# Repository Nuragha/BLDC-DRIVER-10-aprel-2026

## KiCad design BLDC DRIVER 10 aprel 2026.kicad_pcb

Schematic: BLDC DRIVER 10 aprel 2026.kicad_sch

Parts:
C1: 4.7uF 35V; C_1206_3216Metric_Pad1.33x1.80mm_HandSolder
C2, C3, C8, C9, C13, C14: 4.7nF 50V; C_1206_3216Metric_Pad1.33x1.80mm_HandSolder
C4, C6, C11: 22pF; C_0805_2012Metric
C5, C10, C15: 470uF/50V; CP_Elec_10x10.5
C7, C12: 4.7uF 24V; C_1206_3216Metric_Pad1.33x1.80mm_HandSolder
C16, C17, C18: 10nF; C_0805_2012Metric
C19, C28, C29: 100nF/35V; C_1206_3216Metric_Pad1.33x1.80mm_HandSolder
C20, C33: 10nF; C_0603_1608Metric_Pad1.08x0.95mm_HandSolder
C23: 22uF/35V; C_1206_3216Metric_Pad1.33x1.80mm_HandSolder
C24, C26, C32, C37: 100nF; C_1206_3216Metric_Pad1.33x1.80mm_HandSolder
C25, C31: 10uF/35V; C_1206_3216Metric_Pad1.33x1.80mm_HandSolder
C27, C34: 100nF; C_0603_1608Metric_Pad1.08x0.95mm_HandSolder
C36: 22uF/10V; C_1206_3216Metric_Pad1.33x1.80mm_HandSolder
C38, C39: 12pF; C_0805_2012Metric
C40, C41: 100nF; C_0805_2012Metric
D2: MM3Z12; D_SOD-323F
D3, D4, D5: UF4007; D_1206_3216Metric_Pad1.42x1.75mm_HandSolder
D6, D9, D11, D12, D16, D17, D21, D25, D26: Green; LED_0805_2012Metric
D7, D8, D13, D14, D18, D19: SR5100; D_0805_2012Metric_Pad1.15x1.40mm_HandSolder
D22, D23, D24: Red; LED_0805_2012Metric
F1: Fuse_Small; Fuse_1206_3216Metric
HQA1: BSC028N06LS3; TDSON-8-1
HQB1: BSC028N06LS3; TDSON-8-1
HQC1: BSC028N06LS3; TDSON-8-1
J1: Conn_01x02_Socket; TerminalBlock_Phoenix_MKDS-1,5-2-5.08_1x02_P5.08mm_Horizont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
J2: Conn_01x03_Socket; TerminalBlock_Phoenix_MKDS-1,5-3_1x03_P5.00mm_Horizontal
J3: Programing Inputs; PinSocket_1x06_P2.54mm_Vertical_SMD_Pin1Left
L1, L2: 6.8uH/4A; L_6.3x6.3_H3
LQA1: BSC028N06LS3; TDSON-8-1
LQB1: BSC028N06LS3; TDSON-8-1
LQC1: BSC028N06LS3; TDSON-8-1
Q7: IRF4905; TO-220-3_Vertical
Q8, Q9, Q10: BCV29; SOT-89-3
R1, R4, R21, R22, R34, R35, R43: 100k; R_0805_2012Metric_Pad1.20x1.40mm_HandSolder
R2, R3, R19, R20, R32, R33: 10R; R_0805_2012Metric_Pad1.20x1.40mm_HandSolder
R5, R6, R24, R25, R37, R38: R10W1; R_1206_3216Metric_Pad1.30x1.75mm_HandSolder
R7, R17, R30: 1k 0.25W; R_0805_2012Metric_Pad1.20x1.40mm_HandSolder
R8, R62: 330R 0.25W; R_0603_1608Metric_Pad0.98x0.95mm_HandSolder
R10, R29: 330R 0.25W; R_0805_2012Metric_Pad1.20x1.40mm_HandSolder
R11: 140k/1%; R_0603_1608Metric_Pad0.98x0.95mm_HandSolder
R12, R16, R18, R26, R28, R48, R51: 10k; R_0805_2012Metric_Pad1.20x1.40mm_HandSolder
R13, R15, R27, R31, R46, R49: 1k; R_0805_2012Metric_Pad1.20x1.40mm_HandSolder
R14, R23, R36: 10mR; R_Shunt_Vishay_WSKW0612
R40, R41, R42: 10; R_0805_2012Metric_Pad1.20x1.40mm_HandSolder
R44: 2.2k; R_0603_1608Metric_Pad0.98x0.95mm_HandSolder
R45, R47, R50: 220; R_0805_2012Metric_Pad1.20x1.40mm_HandSolder
R52: 10k/1%; R_0603_1608Metric_Pad0.98x0.95mm_HandSolder
R53, R57: 470k/1%; R_0603_1608Metric_Pad0.98x0.95mm_HandSolder
R54, R58: 75k/1%; R_0603_1608Metric_Pad0.98x0.95mm_HandSolder
R55, R59: 0R; R_0603_1608Metric_Pad0.98x0.95mm_HandSolder
R56: 1k; R_0603_1608Metric_Pad0.98x0.95mm_HandSolder
R60: 20k/1%; R_0603_1608Metric_Pad0.98x0.95mm_HandSolder
R61: 62k/1%; R_0603_1608Metric_Pad0.98x0.95mm_HandSolder
R63: 100; R_0805_2012Metric_Pad1.20x1.40mm_HandSolder
R64, R65, R66, R67: 22; R_0805_2012Metric_Pad1.20x1.40mm_HandSolder
SW1: Reset Button; SW_SPST_EVQP2_MiddlePushTravel_H2.5mm
U1, U2, U3: IR2110S; SOIC-16W_7.5x10.3mm_P1.27mm
U5: STM32G431CBTx; LQFP-48_7x7mm_P0.5mm
U6, U7: TPS62933F; SOT-583-8
Y1: 48MHz; Crystal_SMD_0603-2Pin_6.0x3.5mm_HandSoldering

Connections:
+3.3V: C36.1, C37.1, C41.1, D9.2 (A), D11.2 (A), D16.2 (A), D26.2 (A), J2.1, L2.2, Q8.2 (C), Q9.2 (C), Q10.2 (C), R26.2, R61.2, R63.2, U1.11 (VDD), U2.11 (VDD), U3.11 (VDD), U5.21 (VDDA), U5.24 (VDD), U5.36 (VDD), U5.48 (VDD)
+12V: C19.1, C23.1, C24.1, C28.1, C29.1, D3.2 (A), D4.2 (A), D5.2 (A), D6.2 (A), D12.2 (A), D17.2 (A), D25.2 (A), L1.2, R11.2, U1.3 (VCC), U2.3 (VCC), U3.3 (VCC)
+24V: C5.1, C10.1, C15.1, C25.1, C26.1, C31.1, C32.1, D2.1 (K), D21.2 (A), HQA1.5 (D), HQB1.5 (D), HQC1.5 (D), Q7.3 (S), R5.2, R24.2, R37.2, R53.2, R57.2, U6.3 (VIN), U7.3 (VIN)
/ADC_1: C16.1, R40.1, U5.15 (PA7)
/ADC_2: C17.1, R41.1, U5.16 (PB0)
/ADC_3: C18.1, R42.1, U5.27 (PB13)
/Hin_A: R13.1, U5.32 (PA10)
/Hin_B: R15.1, U5.31 (PA9)
/Hin_C: R27.1, U5.30 (PA8)
/Lin_A: U1.14 (LIN), U5.29 (PB15)
/Lin_B: U2.14 (LIN), U5.34 (PA12)
/Lin_C: U3.14 (LIN), U5.33 (PA11)
/MCU_ADC_PH_A: R14.2, R40.2
/MCU_ADC_PH_B: R23.2, R41.2
/MCU_ADC_PH_C: R36.2, R42.2
/NRST: C40.1, R26.1, R66.2, SW1.2, U5.7 (PG10)
/PH_A: C1.2, C2.2, HQA1.1 (S), HQA1.2 (S), HQA1.3 (S), LQA1.5 (D), R1.2, R6.2, U1.6 (VS)
/PH_B: C7.2, C8.2, HQB1.1 (S), HQB1.2 (S), HQB1.3 (S), LQB1.5 (D), R21.2, R25.2, U2.6 (VS)
/PH_C: C12.2, C13.2, HQC1.1 (S), HQC1.2 (S), HQC1.3 (S), LQC1.5 (D), R34.2, R38.2, U3.6 (VS)
/SWCLK: R64.2, U5.38 (PA14)
/SWDIO: R65.2, U5.37 (PA13)
/SWO: R67.2, U5.40 (PB3)
/Shut down_A: Q8.3 (E), R18.2, R45.1, U1.13 (SD)
/Shut down_B: Q9.3 (E), R47.1, R48.2, U2.13 (SD)
/Shut down_C: Q10.3 (E), R50.1, R51.2, U3.13 (SD)
/Speed ccontrol_ADC: J2.2, U5.8 (PA0); also elsewhere on the board
/ir2110 shut down_A: R31.1, U5.9 (PA1)
/ir2110 shut down_B: R46.1, U5.10 (PA2)
/ir2110 shut down_C: R49.1, U5.11 (PA3)
/voltage sensing: U5.28 (PB14)
GND: C4.2, C5.2, C6.2, C10.2, C11.2, C15.2, C16.2, C17.2, C18.2, C19.2, C20.2, C23.2, C24.2, C25.2, C26.2, C28.2, C29.2, C31.2, C32.2, C33.2, C36.2, C37.2, C38.2, C39.2, C40.2, C41.2, D22.1 (K), D23.1 (K), D24.1 (K), J1.2, J2.3, J3.6, R7.1, R8.1, R10.1, R12.1, R14.3, R14.4, R16.1, R17.1, R18.1, R23.3, R23.4, R28.1, R29.1, R30.1, R36.3, R36.4, R43.2, R44.1, R48.1, R51.1, R52.2, R54.1, R55.1, R56.1, R58.1, R59.1, R60.2, R62.1, SW1.1, U1.2 (COM), U1.15 (VSS), U2.2 (COM), U2.15 (VSS), U3.2 (COM), U3.15 (VSS), U5.19 (VSSA), U5.23 (VSS), U5.35 (VSS), U5.47 (VSS), U6.4 (GND), U7.4 (GND); also elsewhere on the board
unnamed: C2.1, R5.1
unnamed: C3.1, R6.1
unnamed: C3.2, LQA1.1 (S), LQA1.2 (S), LQA1.3 (S), R4.2, R14.1
unnamed: C8.1, R24.1
unnamed: C9.1, R25.1
unnamed: C9.2, LQB1.1 (S), LQB1.2 (S), LQB1.3 (S), R22.2, R23.1
unnamed: C13.1, R37.1
unnamed: C14.1, R38.1
unnamed: C14.2, LQC1.1 (S), LQC1.2 (S), LQC1.3 (S), R35.2, R36.1
unnamed: D2.2 (A), Q7.1 (G), R43.1
unnamed: C1.1, D3.1 (K), U1.7 (VB)
unnamed: C7.1, D4.1 (K), U2.7 (VB)
unnamed: C12.1, D5.1 (K), U3.7 (VB)
unnamed: D6.1 (K), R7.2
unnamed: D7.2 (A), HQA1.4 (G), R1.1, R2.2
unnamed: D7.1 (K), R2.1, U1.8 (HO)
unnamed: D8.2 (A), LQA1.4 (G), R3.2, R4.1
unnamed: D8.1 (K), R3.1, U1.1 (LO)
unnamed: D9.1 (K), R8.2
unnamed: D11.1 (K), R10.2
unnamed: D12.1 (K), R17.2
unnamed: D13.2 (A), LQB1.4 (G), R19.2, R22.1
unnamed: D13.1 (K), R19.1, U2.1 (LO)
unnamed: D14.2 (A), HQB1.4 (G), R20.2, R21.1
unnamed: D14.1 (K), R20.1, U2.8 (HO)
unnamed: D16.1 (K), R29.2
unnamed: D17.1 (K), R30.2
unnamed: D18.2 (A), LQC1.4 (G), R32.2, R35.1
unnamed: D18.1 (K), R32.1, U3.1 (LO)
unnamed: D19.2 (A), HQC1.4 (G), R33.2, R34.1
unnamed: D19.1 (K), R33.1, U3.8 (HO)
unnamed: D21.1 (K), R44.2
unnamed: D22.2 (A), R45.2
unnamed: D23.2 (A), R47.2
unnamed: D24.2 (A), R50.2
unnamed: D25.1 (K), R56.2
unnamed: D26.1 (K), R62.2
unnamed: F1.1, J1.1
unnamed: J3.1, R63.1
unnamed: J3.2, R64.1
unnamed: J3.3, R65.1
unnamed: J3.4, R66.1
unnamed: J3.5, R67.1
unnamed: F1.2, Q7.2 (D)
unnamed: Q8.1 (B), R31.2
unnamed: Q9.1 (B), R46.2
unnamed: Q10.1 (B), R49.2
unnamed: C4.1, R12.2, R13.2, U1.12 (HIN)
unnamed: C6.1, R15.2, R16.2, U2.12 (HIN)
unnamed: C11.1, R27.2, R28.2, U3.12 (HIN)
unnamed: C38.1, U5.5 (PF0), Y1.1
unnamed: C39.1, U5.6 (PF1), Y1.2
unnamed: C27.1, U6.6 (BST)
unnamed: R53.1, R54.2, U6.2 (EN)
unnamed: R11.1, R52.1, U6.8 (FB)
unnamed: R55.2, U6.1 (RT)
unnamed: C20.1, U6.7 (SS)
unnamed: C27.2, L1.1, U6.5 (SW)
unnamed: C34.1, U7.6 (BST)
unnamed: R57.1, R58.2, U7.2 (EN)
unnamed: R60.1, R61.1, U7.8 (FB)
unnamed: R59.2, U7.1 (RT)
unnamed: C33.1, U7.7 (SS)
unnamed: C34.2, L2.1, U7.5 (SW)

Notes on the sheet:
input protection circuit
3.3V DC-DC Buck converter
In 24V
adc_1 adc_2 and adc_3 connecting op amp1,2and 3 Non-Inverting pins
RT=0R and 1.2MHz
IR2110 protect
Vout=0.8*(1+R1/R2)
12V DC-DC Buck converter
speed control input
ok inducator
SENSING LOW PASS FILTERS
12V out
3.3V out
out motor drive phases
3.28V feedback
12V feedback

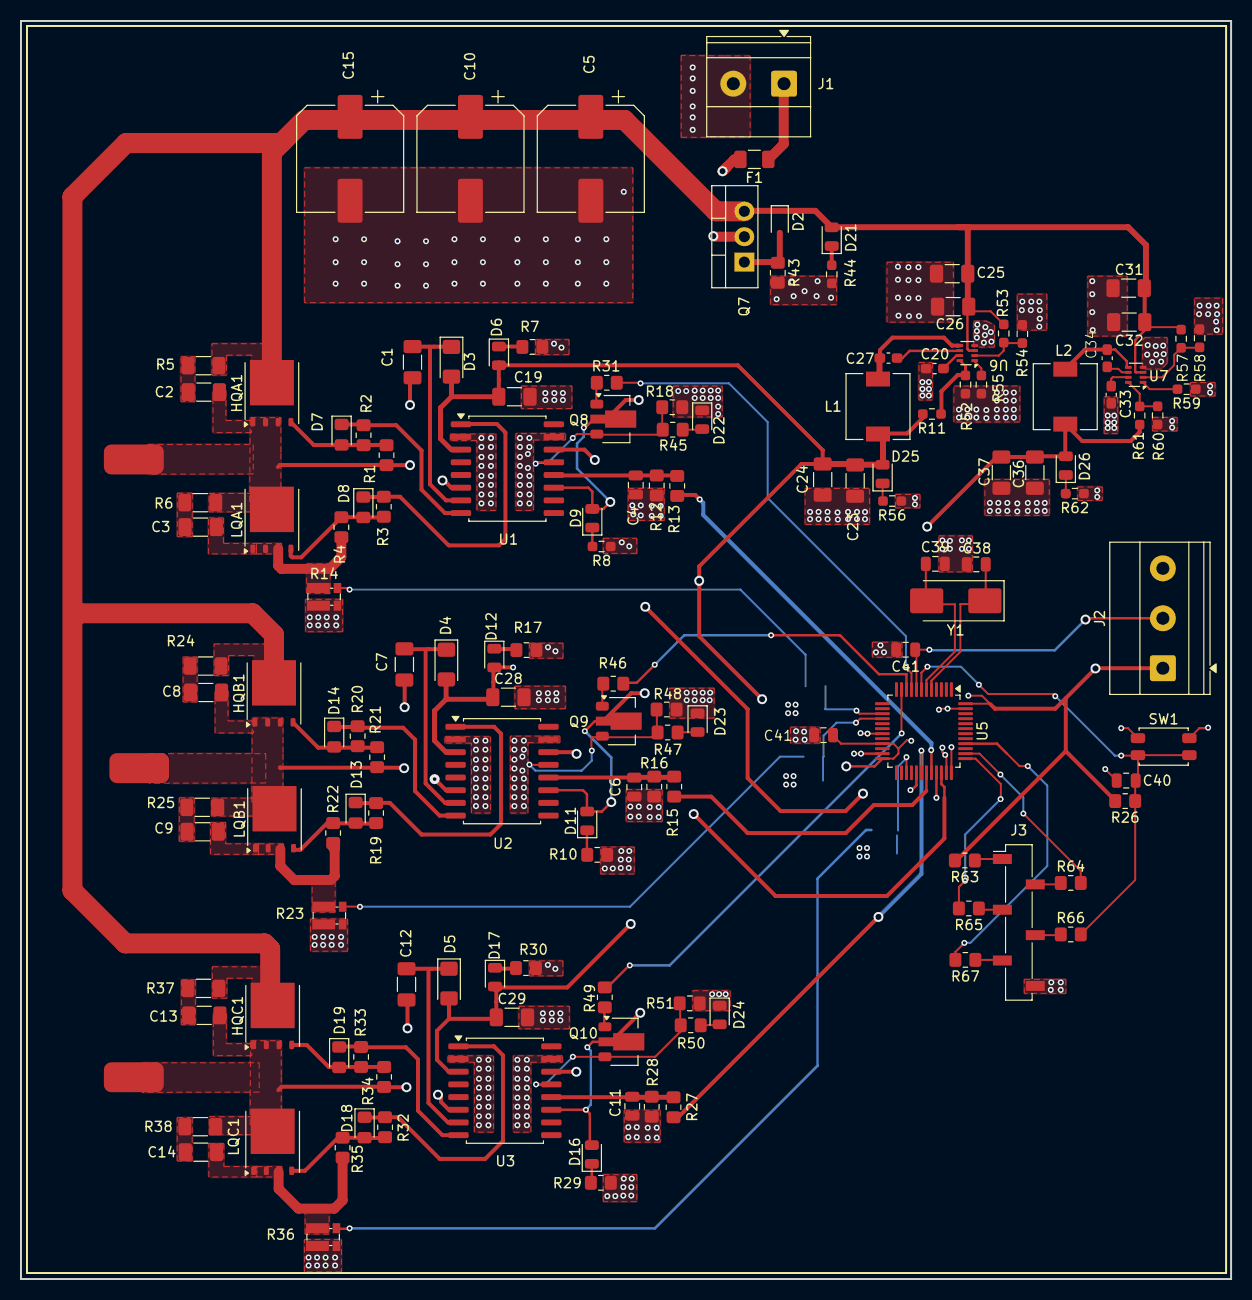
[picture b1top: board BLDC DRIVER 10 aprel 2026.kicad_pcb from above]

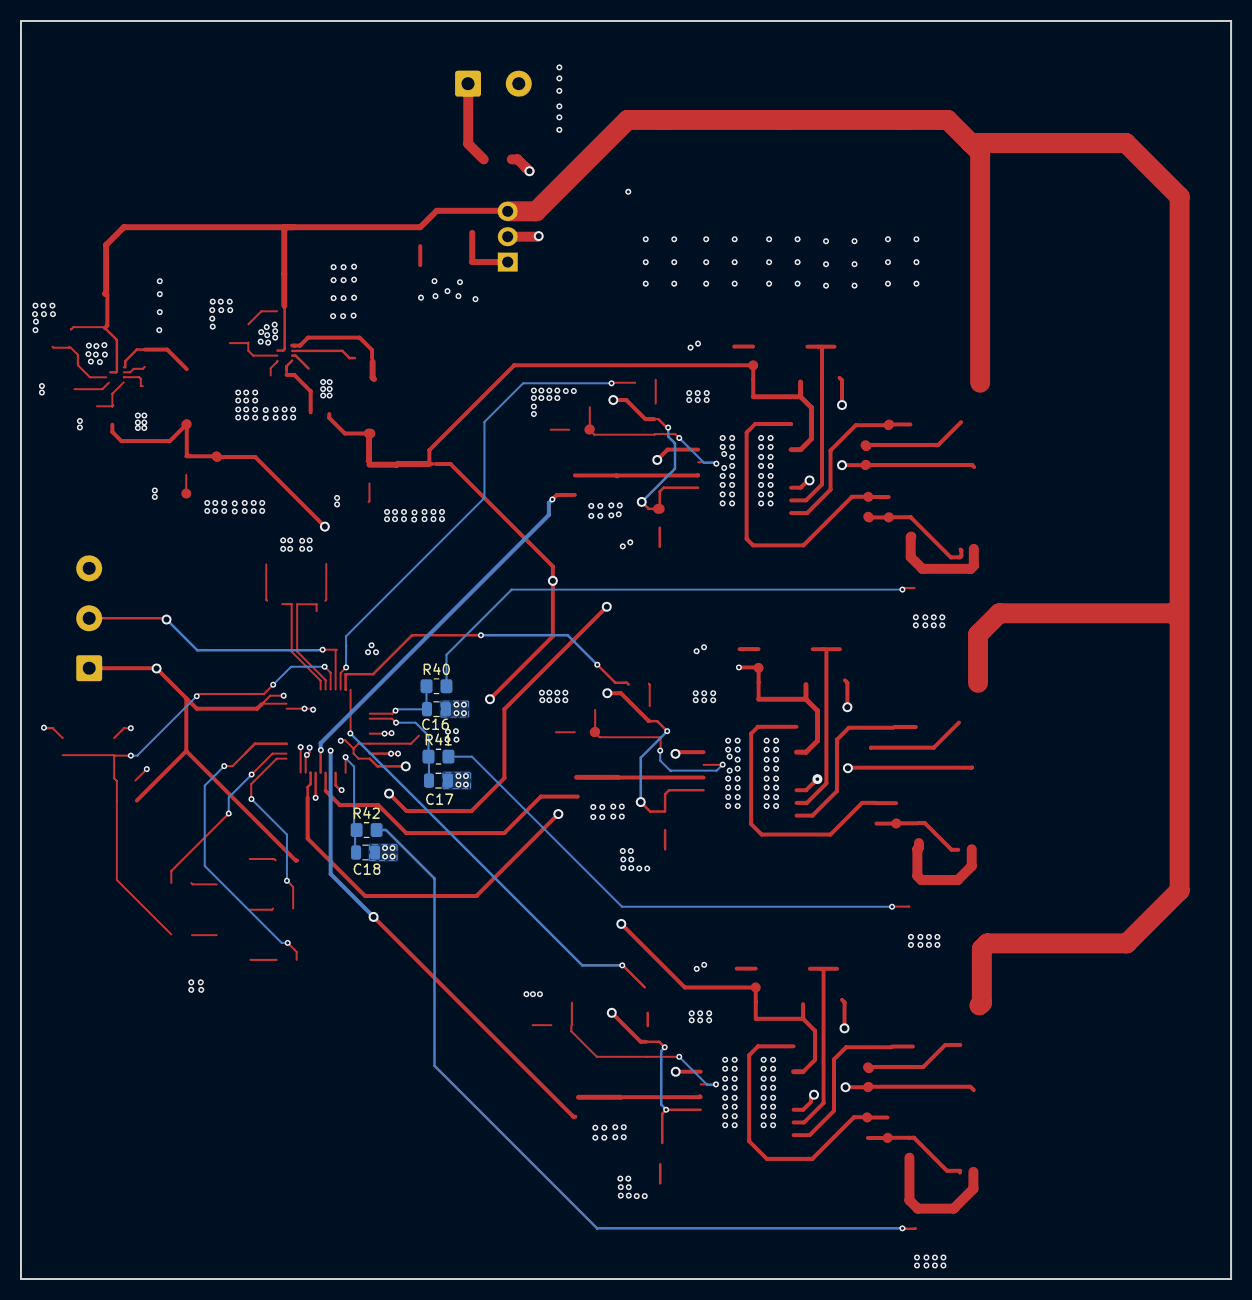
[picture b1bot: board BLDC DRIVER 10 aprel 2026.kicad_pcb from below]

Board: 4 copper layers, 121.1 x 125.9 mm, 149 parts (6 on the bottom side), 94 nets.

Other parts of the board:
C41#2: 100nF; C_0805_2012Metric

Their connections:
/Speed ccontrol_ADC: C41#2.1; also elsewhere on the board
GND: C41#2.2; also elsewhere on the board
